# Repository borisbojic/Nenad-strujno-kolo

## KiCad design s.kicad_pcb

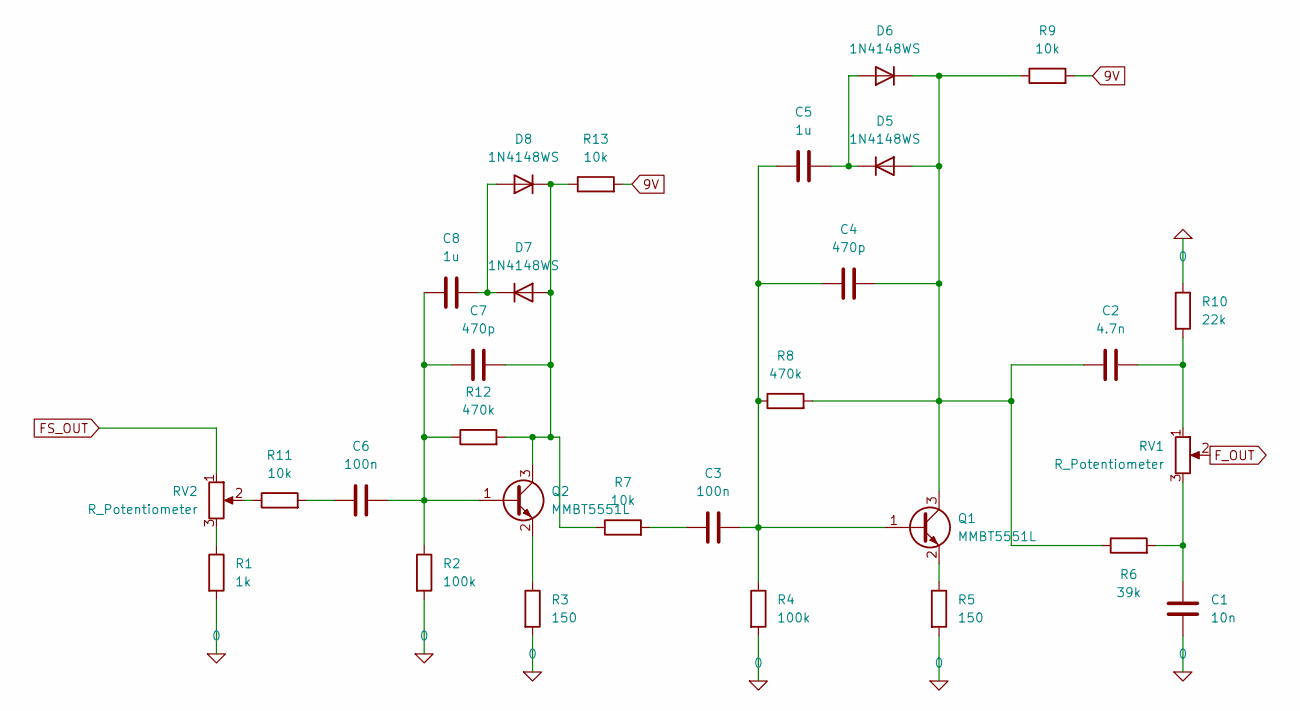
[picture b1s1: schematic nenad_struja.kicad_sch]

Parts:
C1: 10n
C2: 4.7n
C3, C6: 100n
C4, C7: 470p
C5, C8: 1u
D5, D6, D7, D8: 1N4148WS; D_SOD-323
Q1, Q2: MMBT5551L; SOT-23
R1: 1k
R2, R4: 100k
R3, R5: 150
R6: 39k
R7, R9, R11, R13: 10k
R8, R12: 470k
R10: 22k
RV1, RV2: R_Potentiometer

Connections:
9V: R9.2, R13.2
FS_OUT: RV2.1
F_OUT: RV1.2
GND: C1.2, R1.2, R2.2, R3.2, R4.2, R5.2, R10.1
unnamed: C1.1, R6.2, RV1.3
unnamed: C2.2, R10.2, RV1.1
unnamed: C3.1, R7.2
unnamed: C6.1, R11.2
unnamed: C2.1, C4.2, D5.2 (A), D6.1 (K), Q1.3 (C), R6.1, R8.2, R9.1
unnamed: C5.2, D5.1 (K), D6.2 (A)
unnamed: C7.2, D7.2 (A), D8.1 (K), Q2.3 (C), R7.1, R12.2, R13.1
unnamed: C8.2, D7.1 (K), D8.2 (A)
unnamed: C3.2, C4.1, C5.1, Q1.1 (B), R4.1, R8.1
unnamed: Q1.2 (E), R5.1
unnamed: C6.2, C7.1, C8.1, Q2.1 (B), R2.1, R12.1
unnamed: Q2.2 (E), R3.1
unnamed: R1.1, RV2.3
unnamed: R11.1, RV2.2

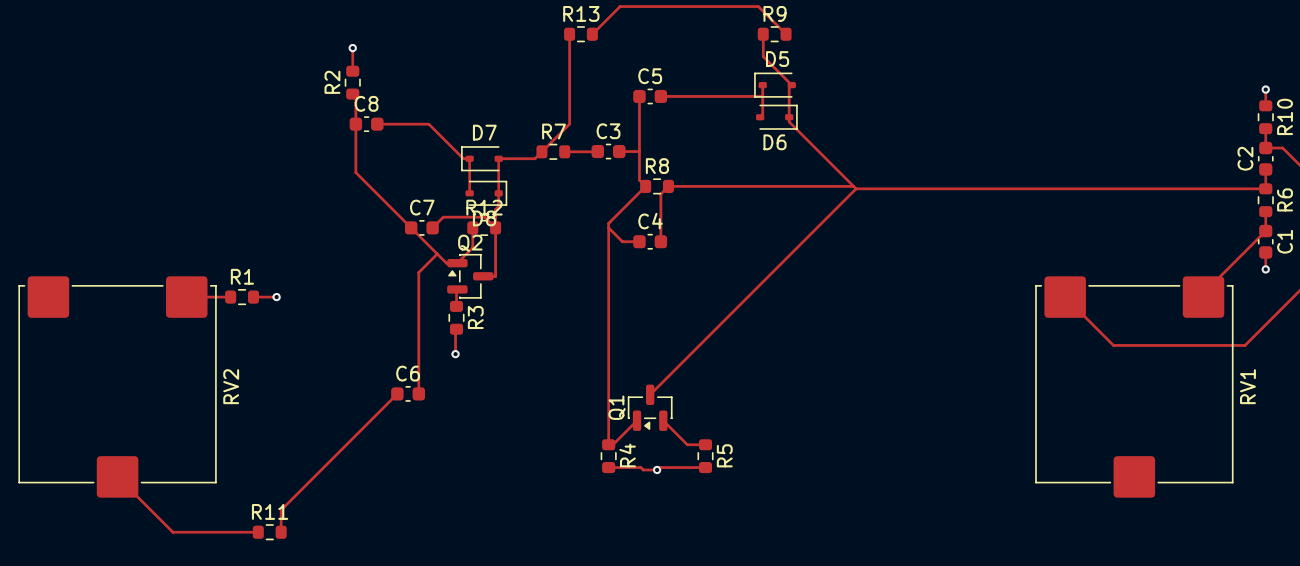
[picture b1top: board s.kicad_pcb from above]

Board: 2 copper layers, 29 parts (0 on the bottom side), 16 nets.

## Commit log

2026-04-17 jfjjfjf JEJJJJJJJJJ!!!! DODOA SSAM!!!!!! SVE!!!!!!!!!!!!!!!!
2026-04-19 dodao pcb dizajn
